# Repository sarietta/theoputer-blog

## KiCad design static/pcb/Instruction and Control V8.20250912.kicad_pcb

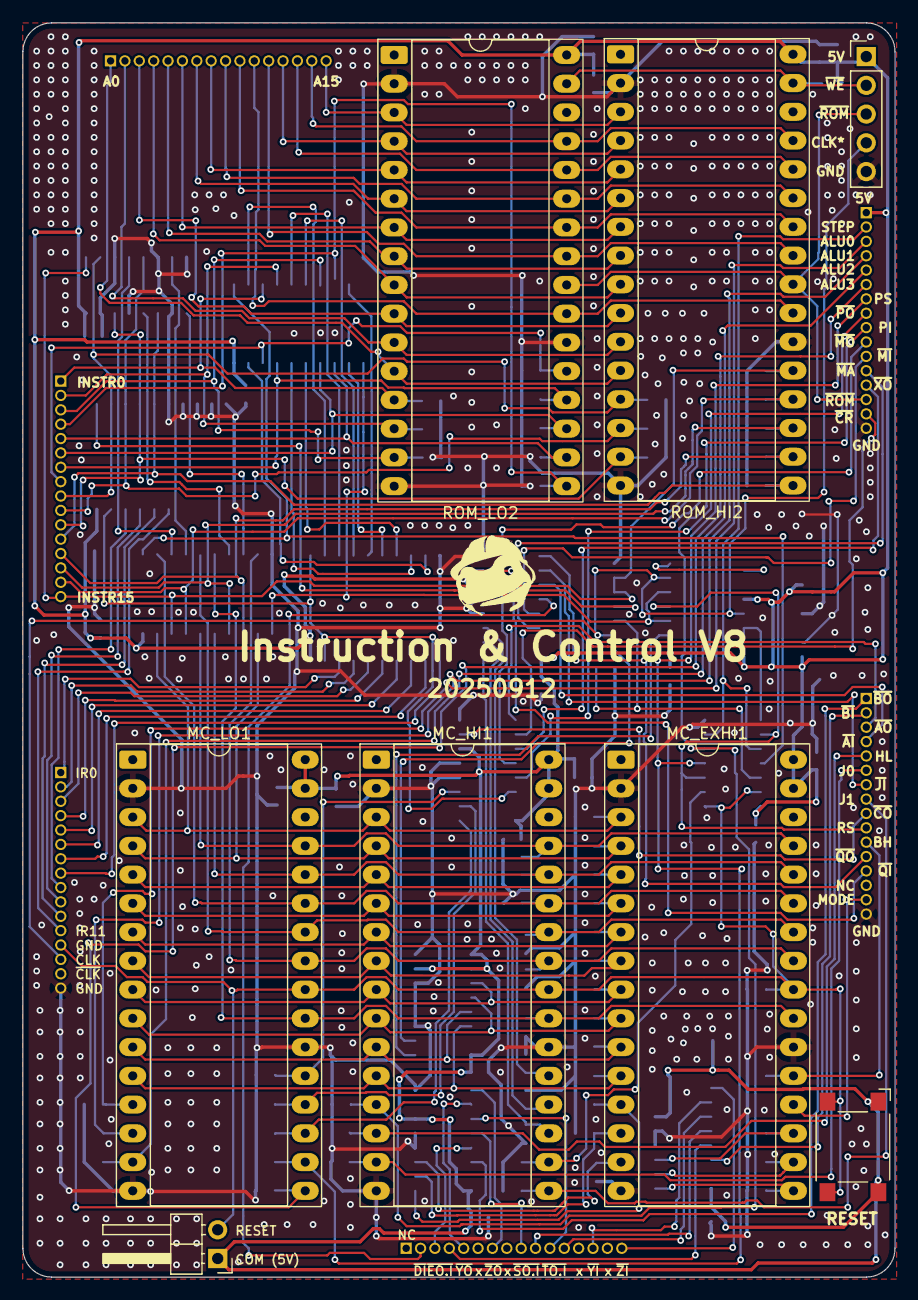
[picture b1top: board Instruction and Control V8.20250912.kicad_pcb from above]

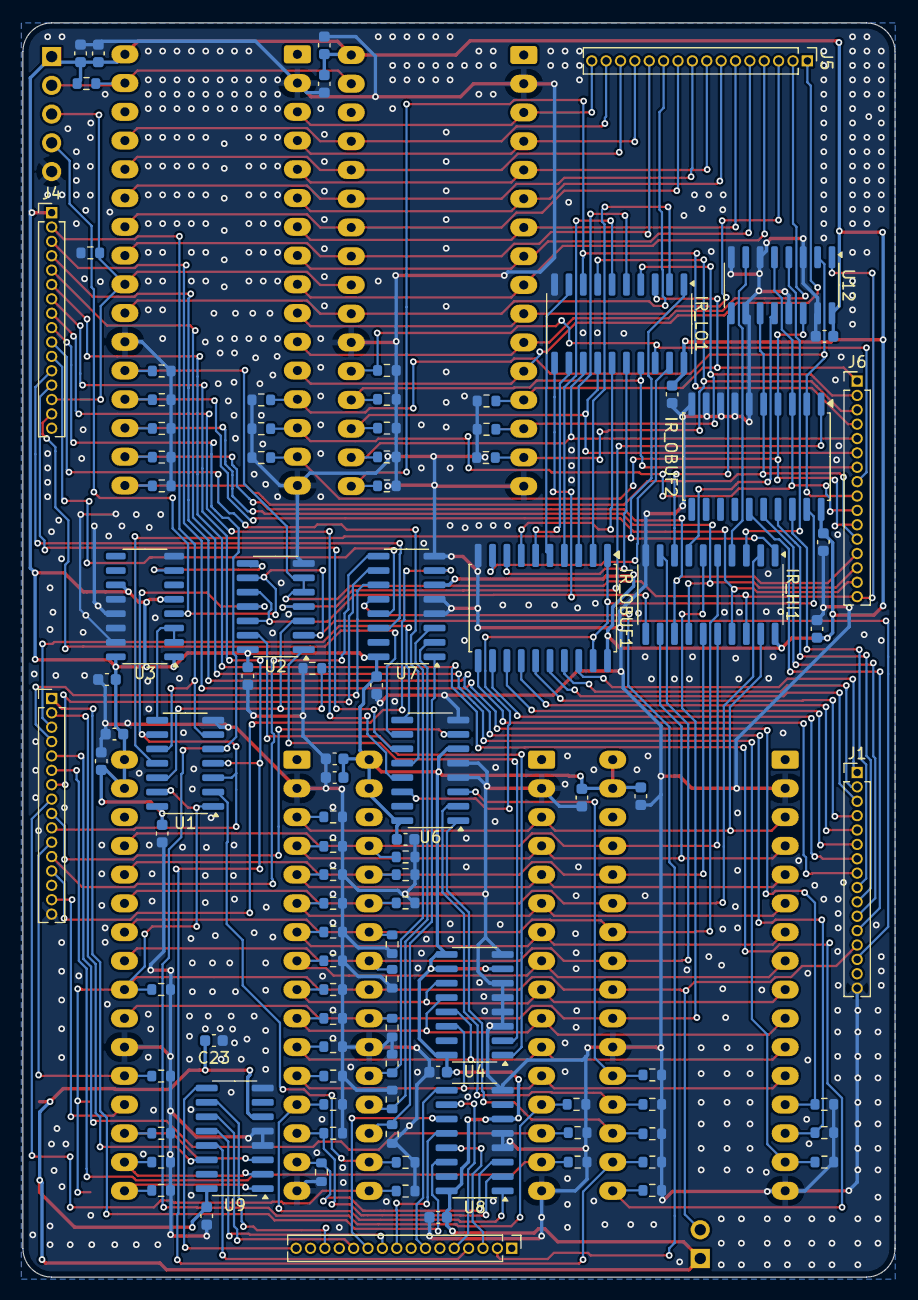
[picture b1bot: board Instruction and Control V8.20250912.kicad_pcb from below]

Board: 2 copper layers, 77.1 x 110.8 mm, 109 parts (101 on the bottom side), 138 nets.

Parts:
C1, C19, C20, C21, C22: 1uF; C_0603_1608Metric
C2, C3, C4, C5, C6, C7, C8, C9, C10, C11, C12, C13, C14, C15, C16, C17, C18, C23: 0.1uF; C_0603_1608Metric
IR_HI1: 74HCT374; SO-20_5.3x12.6mm_P1.27mm
IR_LO1: 74HCT374; SO-20_5.3x12.6mm_P1.27mm
IR_OBUF1, IR_OBUF2: 74HCT541D,653; SOIC-20W_7.5x12.8mm_P1.27mm
J1, J3, J4, J5, J6, J9: Conn_01x16; PinHeader_1x16_P1.27mm_Vertical
J2: Conn_01x05; PinHeader_1x05_P2.54mm_Vertical
J7: Conn_01x02; PinHeader_1x02_P2.54mm_Horizontal
MC_EXHI1: SST39SF010; DIP-32_W15.24mm_Socket_LongPads
MC_HI1: SST39SF010; DIP-32_W15.24mm_Socket_LongPads
MC_LO1: SST39SF010; DIP-32_W15.24mm_Socket_LongPads
R1, R3, R4, R5, R6, R7, R8, R9, R10, R11, R12, R13, R14, R15, R16, R17, R18, R19, R20, R21, R22, R23, R24, R25, R26, R27, R28, R29, R30, R31, R32, R33, R34, R35, R36, R37, R38, R39, R40, R41, R42, R47, R48, R49, R50, R51, R52, R53, R54, R55, R56, R57, R58, R59, R60, R61, R62, R66, R67: 1K; R_0603_1608Metric
ROM_HI2: SST39SF010; DIP-32_W15.24mm_Socket_LongPads
ROM_LO2: SST39SF010; DIP-32_W15.24mm_Socket_LongPads
SW1: SW_Omron_B3FS; SW_SPST_Omron_B3FS-100xP
U1: SN74ACT32DR; SOIC-14_3.9x8.7mm_P1.27mm
U2: SN74HCT02DR; SOIC-14_3.9x8.7mm_P1.27mm
U3: 74HC109D,653; SO-16_3.9x9.9mm_P1.27mm
U4: 74ACT161; SOIC-16_3.9x9.9mm_P1.27mm
U6, U7, U8, U9: SN74HCT138DR; SOIC-16_3.9x9.9mm_P1.27mm
U12: SN74HC257DR; SOIC-16_3.9x9.9mm_P1.27mm

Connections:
+5V: C1.1, C2.1, C3.1, C4.1, C5.1, C6.1, C7.1, C8.1, C9.1, C10.1, C11.1, C12.1, C13.1, C14.1, C15.1, C16.1, C17.1, C18.1, C19.1, C20.1, C21.1, C22.1, C23.1, IR_HI1.20 (VCC), IR_LO1.20 (VCC), IR_OBUF1.20 (VCC), IR_OBUF2.20 (VCC), J2.1, J4.1, J7.1, MC_EXHI1.31 (PGM), MC_EXHI1.32 (VCC), MC_HI1.31 (PGM), MC_HI1.32 (VCC), MC_LO1.31 (PGM), MC_LO1.32 (VCC), R66.2, ROM_HI2.32 (VCC), ROM_LO2.32 (VCC), SW1.1, U1.14 (VCC), U2.14 (VCC), U3.1 (~R), U3.5 (~S), U3.11 (~S), U3.16 (VCC), U4.7 (CEP), U4.9 (~PE), U4.10 (CET), U4.16 (VCC), U6.6 (E2), U6.16 (VCC), U7.6 (E2), U7.16 (VCC), U8.6 (E2), U8.16 (VCC), U9.6 (E2), U9.16 (VCC), U12.16 (VCC)
/ADDR0: J5.1, ROM_HI2.12 (A0), ROM_LO2.12 (A0)
/ADDR1: J5.2, ROM_HI2.11 (A1), ROM_LO2.11 (A1)
/ADDR2: J5.3, ROM_HI2.10 (A2), ROM_LO2.10 (A2)
/ADDR3: J5.4, ROM_HI2.9 (A3), ROM_LO2.9 (A3)
/ADDR4: J5.5, ROM_HI2.8 (A4), ROM_LO2.8 (A4)
/ADDR5: J5.6, ROM_HI2.7 (A5), ROM_LO2.7 (A5)
/ADDR6: J5.7, ROM_HI2.6 (A6), ROM_LO2.6 (A6)
/ADDR7: J5.8, ROM_HI2.5 (A7), ROM_LO2.5 (A7)
/ADDR8: J5.9, ROM_HI2.27 (A8), ROM_LO2.27 (A8)
/ADDR9: J5.10, ROM_HI2.26 (A9), ROM_LO2.26 (A9)
/ADDR10: J5.11, ROM_HI2.23 (A10), ROM_LO2.23 (A10)
/ADDR11: J5.12, ROM_HI2.25 (A11), ROM_LO2.25 (A11)
/ADDR12: J5.13, ROM_HI2.4 (A12), ROM_LO2.4 (A12)
/ADDR13: J5.14, ROM_HI2.28 (A13), ROM_LO2.28 (A13)
/ADDR14: J5.15, ROM_HI2.29 (A14), ROM_LO2.29 (A14)
/ADDR15: J5.16, ROM_HI2.3 (A15), ROM_LO2.3 (A15)
/ALU0: J4.3, MC_LO1.13 (D0), R38.1
/ALU1: J4.4, MC_LO1.14 (D1), R36.1
/ALU2: J4.5, MC_LO1.15 (D2), R34.1
/ALU3: J4.6, MC_LO1.17 (D3), R33.1
/BO_HI: J3.11, MC_EXHI1.21 (D7), R32.1
/CLK: J1.14, J2.4, U2.2, U2.9, U3.4 (C)
/DISABLE_ROM: J2.3, J4.14, R67.2, ROM_HI2.24 (OE), ROM_LO2.24 (OE)
/EXEC_MODE: J3.15, MC_EXHI1.20 (D6)
/EXT_IN0: MC_EXHI1.17 (D3), R39.1, U9.1 (A0)
/EXT_IN1: MC_EXHI1.18 (D4), R37.1, U9.2 (A1)
/EXT_IN2: MC_EXHI1.19 (D5), R35.1, U9.3 (A2)
/EXT_OUT0: MC_EXHI1.13 (D0), R42.1, U8.1 (A0)
/EXT_OUT1: MC_EXHI1.14 (D1), R41.1, U8.2 (A1)
/EXT_OUT2: MC_EXHI1.15 (D2), R40.1, U8.3 (A2)
/HL: J3.5, MC_HI1.14 (D1), R26.1
/IN0: MC_HI1.19 (D5), R22.1, U7.1 (A0)
/IN1: MC_HI1.20 (D6), R21.1, U7.2 (A1)
/IN2: MC_HI1.21 (D7), R20.1, U7.3 (A2)
/INHIBIT_MC: R1.1, U1.12, U2.3
/INSTR0: IR_LO1.3 (D0), J6.1, R62.1, ROM_LO2.13 (D0)
/INSTR1: IR_LO1.4 (D1), J6.2, R61.1, ROM_LO2.14 (D1)
/INSTR2: IR_LO1.7 (D2), J6.3, R60.1, ROM_LO2.15 (D2)
/INSTR3: IR_LO1.8 (D3), J6.4, R59.1, ROM_LO2.17 (D3)
/INSTR4: IR_LO1.13 (D4), J6.5, R58.1, ROM_LO2.18 (D4)
/INSTR5: IR_LO1.14 (D5), J6.6, R57.1, ROM_LO2.19 (D5)
/INSTR6: IR_LO1.17 (D6), J6.7, R56.1, ROM_LO2.20 (D6)
/INSTR7: IR_LO1.18 (D7), J6.8, R55.1, ROM_LO2.21 (D7)
/INSTR8: IR_OBUF2.2 (A0), J6.9, R54.1, ROM_HI2.13 (D0), U12.2 (I0a)
/INSTR9: IR_OBUF2.3 (A1), J6.10, R53.1, ROM_HI2.14 (D1), U12.5 (I0b)
/INSTR10: IR_OBUF2.4 (A2), J6.11, R52.1, ROM_HI2.15 (D2), U12.14 (I0c)
/INSTR11: IR_OBUF2.5 (A3), J6.12, R51.1, ROM_HI2.17 (D3), U12.11 (I0d)
/INSTR12: IR_HI1.13 (D4), J6.13, R50.1, ROM_HI2.18 (D4)
/INSTR13: IR_HI1.14 (D5), J6.14, R49.1, ROM_HI2.19 (D5)
/INSTR14: IR_HI1.17 (D6), J6.15, R48.1, ROM_HI2.20 (D6)
/INSTR15: IR_HI1.18 (D7), J6.16, R47.1, ROM_HI2.21 (D7), U2.5, U2.6, U12.1 (S)
/IR_OUT0: IR_OBUF1.18 (Y0), J1.1
/IR_OUT1: IR_OBUF1.17 (Y1), J1.2
/IR_OUT2: IR_OBUF1.16 (Y2), J1.3
/IR_OUT3: IR_OBUF1.15 (Y3), J1.4
/IR_OUT4: IR_OBUF1.14 (Y4), J1.5
/IR_OUT5: IR_OBUF1.13 (Y5), J1.6
/IR_OUT6: IR_OBUF1.12 (Y6), J1.7
/IR_OUT7: IR_OBUF1.11 (Y7), J1.8
/IR_OUT8: IR_OBUF2.18 (Y0), J1.9
/IR_OUT9: IR_OBUF2.17 (Y1), J1.10
/IR_OUT10: IR_OBUF2.16 (Y2), J1.11
/IR_OUT11: IR_OBUF2.15 (Y3), J1.12
/J0: J3.6, MC_HI1.15 (D2), R25.1
/J1: J3.8, MC_HI1.17 (D3), R24.1
/MC0: MC_EXHI1.12 (A0), MC_HI1.12 (A0), MC_LO1.12 (A0), R19.1, U4.14 (Q0)
/MC1: MC_EXHI1.11 (A1), MC_HI1.11 (A1), MC_LO1.11 (A1), R18.1, U4.13 (Q1)
/MC2: MC_EXHI1.10 (A2), MC_HI1.10 (A2), MC_LO1.10 (A2), R17.1, U4.12 (Q2)
/MC3: MC_EXHI1.9 (A3), MC_HI1.9 (A3), MC_LO1.9 (A3), R16.1, U4.11 (Q3)
/MC4: MC_EXHI1.8 (A4), MC_HI1.8 (A4), MC_LO1.8 (A4), R15.1
/MC5: MC_EXHI1.7 (A5), MC_HI1.7 (A5), MC_LO1.7 (A5), R14.1
/MC6: MC_EXHI1.6 (A6), MC_HI1.6 (A6), MC_LO1.6 (A6), R13.1
/MC7: MC_EXHI1.5 (A7), MC_HI1.5 (A7), MC_LO1.5 (A7), R12.1
/MC8: IR_HI1.2 (O0), MC_EXHI1.27 (A8), MC_HI1.27 (A8), MC_LO1.27 (A8), R11.1
/MC9: IR_HI1.5 (O1), MC_EXHI1.26 (A9), MC_HI1.26 (A9), MC_LO1.26 (A9), R10.1
/MC10: IR_HI1.6 (O2), MC_EXHI1.23 (A10), MC_HI1.23 (A10), MC_LO1.23 (A10), R9.1
/MC11: IR_HI1.9 (O3), MC_EXHI1.25 (A11), MC_HI1.25 (A11), MC_LO1.25 (A11), R8.1
/MC12: IR_HI1.12 (O4), MC_EXHI1.4 (A12), MC_HI1.4 (A12), MC_LO1.4 (A12), R7.1
/MC13: IR_HI1.15 (O5), MC_EXHI1.28 (A13), MC_HI1.28 (A13), MC_LO1.28 (A13), R6.1
/MC14: IR_HI1.16 (O6), MC_EXHI1.29 (A14), MC_HI1.29 (A14), MC_LO1.29 (A14), R5.1
/MC15: IR_HI1.19 (O7), MC_EXHI1.3 (A15), MC_HI1.3 (A15), MC_LO1.3 (A15), R4.1
/OUT0: MC_LO1.19 (D5), R30.1, U6.1 (A0)
/OUT1: MC_LO1.20 (D6), R29.1, U6.2 (A1)
/OUT2: MC_LO1.21 (D7), R28.1, U6.3 (A2)
/PI: J4.9, MC_HI1.13 (D0), R27.1, U1.5
/PS: J4.7, MC_LO1.18 (D4), R31.1, U1.4
/RS: J3.10, U1.3, U1.9, U2.11
/RS1^{*}: MC_HI1.18 (D4), R23.1, U1.2
/RS2^{*}: J1.13, J7.2, MC_EXHI1.24 (OE), MC_HI1.24 (OE), MC_LO1.24 (OE), R3.2, SW1.2, U1.1, U1.13
/STEP: J4.2, U1.6, U1.10
/~AI: J3.4, U7.11 (~Y4)
/~AO: J3.3, U6.9 (~Y6)
/~BI: J3.2, U9.14 (~Y1)
/~BO: J3.1, U8.14 (~Y1)
/~CO: J3.9, U6.7 (~Y7)
/~CR: J4.15, U6.10 (~Y5)
/~DI: J9.2, U7.12 (~Y3)
/~EI: J9.4, U9.13 (~Y2)
/~EO: J9.3, U8.13 (~Y2)
/~IO: IR_OBUF1.1 (G1), IR_OBUF1.19 (G2), IR_OBUF2.19 (G2), U6.14 (~Y1)
/~JI: J3.7, U7.10 (~Y5)
/~MA: J4.12, U7.14 (~Y1)
/~MI: J4.11, U7.13 (~Y2)
/~MO: J4.10, U6.12 (~Y3)
/~PO: J4.8, U6.13 (~Y2)
/~QI: J3.13, U7.7 (~Y7)
/~QO: J3.12, U7.9 (~Y6)
/~RESET_MC_COUNTER_NEXT_DOWNCLK: U2.8, U3.7 (~Q)
/~RESET_MC_COUNTER: U2.13, U4.1 (~MR)
/~ROM_WE: J2.2, R66.1, ROM_HI2.31 (PGM), ROM_LO2.31 (PGM)
/~SI: J9.10, U9.12 (~Y3)
/~SO: J9.9, U8.12 (~Y3)
/~TI: J9.12, U9.11 (~Y4)
/~TO: J9.11, U8.11 (~Y4)
/~XO: J4.13, U6.11 (~Y4)
/~YI: J9.14, U9.10 (~Y5)
/~YO: J9.5, U8.10 (~Y5)
/~ZI: J9.16, U9.9 (~Y6)
/~ZO: J9.7, U8.9 (~Y6)
/↓LATCH_INSTRUCTION: IR_HI1.11 (Cp), IR_LO1.11 (Cp), U2.10, U2.12
GND: C1.2, C2.2, C3.2, C4.2, C5.2, C6.2, C7.2, C8.2, C9.2, C10.2, C11.2, C12.2, C13.2, C14.2, C15.2, C16.2, C17.2, C18.2, C19.2, C20.2, C21.2, C22.2, C23.2, IR_HI1.10 (GND), IR_LO1.10 (GND), IR_OBUF1.10 (GND), IR_OBUF2.6 (A4), IR_OBUF2.7 (A5), IR_OBUF2.8 (A6), IR_OBUF2.9 (A7), IR_OBUF2.10 (GND), J1.16, J2.5, J3.16, J4.16, MC_EXHI1.2 (A16), MC_EXHI1.16 (GND), MC_EXHI1.22 (CE), MC_HI1.2 (A16), MC_HI1.16 (GND), MC_HI1.22 (CE), MC_LO1.2 (A16), MC_LO1.16 (GND), MC_LO1.22 (CE), R1.2, R3.1, R4.2, R5.2, R6.2, R7.2, R8.2, R9.2, R10.2, R11.2, R12.2, R13.2, R14.2, R15.2, R16.2, R17.2, R18.2, R19.2, R20.2, R21.2, R22.2, R23.2, R24.2, R25.2, R26.2, R27.2, R28.2, R29.2, R30.2, R31.2, R32.2, R33.2, R34.2, R35.2, R36.2, R37.2, R38.2, R39.2, R40.2, R41.2, R42.2, R47.2, R48.2, R49.2, R50.2, R51.2, R52.2, R53.2, R54.2, R55.2, R56.2, R57.2, R58.2, R59.2, R60.2, R61.2, R62.2, R67.1, ROM_HI2.2 (A16), ROM_HI2.16 (GND), ROM_HI2.22 (CE), ROM_LO2.2 (A16), ROM_LO2.16 (GND), ROM_LO2.22 (CE), U1.7 (GND), U2.7 (GND), U3.8 (GND), U3.12 (C), U3.13 (~K), U3.14 (J), U3.15 (~R), U4.3 (D0), U4.4 (D1), U4.5 (D2), U4.6 (D3), U4.8 (GND), U6.4 (~E0), U6.5 (~E1), U6.8 (GND), U7.4 (~E0), U7.5 (~E1), U7.8 (GND), U8.4 (~E0), U8.5 (~E1), U8.8 (GND), U9.4 (~E0), U9.5 (~E1), U9.8 (GND), U12.3 (I1a), U12.6 (I1b), U12.8 (GND), U12.10 (I1d), U12.13 (I1c), U12.15 (OE)
unnamed: IR_HI1.3 (D0), U12.4 (Za)
unnamed: IR_HI1.4 (D1), U12.7 (Zb)
unnamed: IR_HI1.7 (D2), U12.12 (Zc)
unnamed: IR_HI1.8 (D3), U12.9 (Zd)
unnamed: IR_HI1.1 (OE), IR_LO1.1 (OE), U1.11
unnamed: IR_LO1.2 (O0), IR_OBUF1.2 (A0)
unnamed: IR_LO1.5 (O1), IR_OBUF1.3 (A1)
unnamed: IR_LO1.6 (O2), IR_OBUF1.4 (A2)
unnamed: IR_LO1.9 (O3), IR_OBUF1.5 (A3)
unnamed: IR_LO1.12 (O4), IR_OBUF1.6 (A4)
unnamed: IR_LO1.15 (O5), IR_OBUF1.7 (A5)
unnamed: IR_LO1.16 (O6), IR_OBUF1.8 (A6)
unnamed: IR_LO1.19 (O7), IR_OBUF1.9 (A7)
unnamed: IR_OBUF2.1 (G1), U2.4
unnamed: U1.8, U3.2 (J), U3.3 (~K)
unnamed: U2.1, U4.2 (CP)

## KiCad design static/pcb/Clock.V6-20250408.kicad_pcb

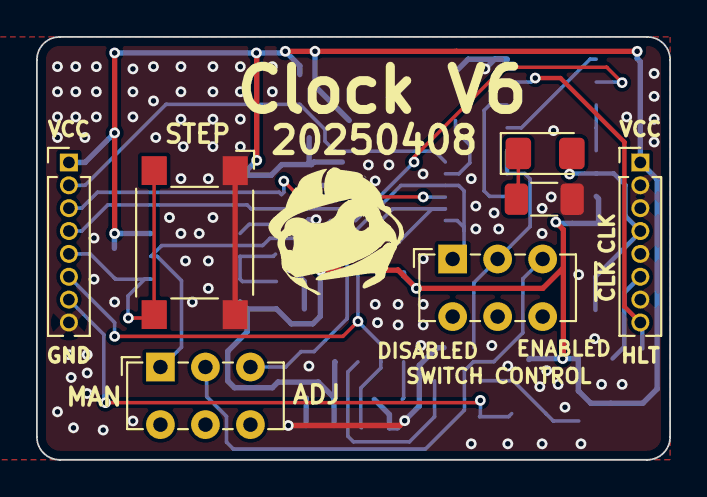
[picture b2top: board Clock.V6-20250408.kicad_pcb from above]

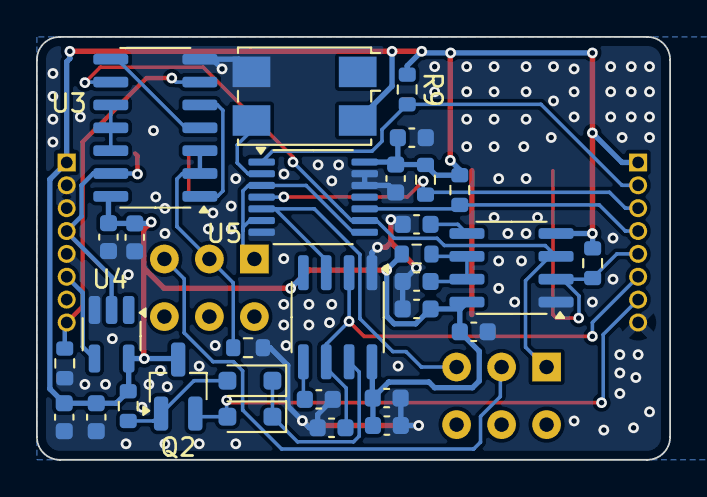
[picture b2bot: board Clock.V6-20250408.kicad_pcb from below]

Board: 4 copper layers, 35.2 x 23.5 mm, 38 parts (31 on the bottom side), 26 nets.

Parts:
C1, C2, C5, C10, C12, C14: 1uF; C_0603_1608Metric
C3, C6: 0.01uF; C_0603_1608Metric
C4, C9, C11, C13, C15: 0.1uF; C_0603_1608Metric
C7: 22uF; C_0603_1608Metric
D1, D2: 1N5819WS; D_SOD-323_HandSoldering
D3: LED; LED_1206_3216Metric_Pad1.42x1.75mm_HandSolder
J7, J8: Conn_01x08; PinHeader_1x08_P1.27mm_Vertical
Q2: MMBT3904; SOT-23_Handsoldering
R1, R5, R6, R7, R8, R9: 1K; R_0603_1608Metric
R2, R3: 10K; R_0603_1608Metric
R4: 1K; R_1206_3216Metric_Pad1.30x1.75mm_HandSolder
SW_EN1: SW_SPDT; SW_E-Switch_EG1271_SPDT
SW_MAN_OR_ADJ1: SW_SPDT; SW_E-Switch_EG1271_SPDT
SW_STEP_1: SW_Omron_B3FS; SW_SPST_Omron_B3FS-100xP
U1, U2: TLC555xD; SOIC-8_3.9x4.9mm_P1.27mm
U3: SN74HCT02DR; SOIC-14_3.9x8.7mm_P1.27mm
U4: SN74AHCT1G04DBVR; SOT-23-5_HandSoldering
U5: SN74AHCT125PWR; TSSOP-14_4.4x5mm_P0.65mm
X1: S7D1.843200A20F30T; Crystal_SMD_7050-4Pin_7.0x5.0mm

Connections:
+5V: C1.1, C4.1, C5.1, C9.1, C10.1, C11.1, C12.1, C13.1, C14.1, C15.1, J7.1, J8.1, Q2.3 (C), R1.1, R2.1, R3.1, R6.1, R8.1, R9.1, U1.4 (R), U1.8 (VCC), U2.4 (R), U2.8 (VCC), U3.14 (VCC), U4.5 (VCC), U5.14 (VCC), X1.4 (VCC)
/ADJ_GND: C2.1, J7.6, U1.2 (TR), U1.6 (THR)
/ADJ_VCC: D2.2 (A), J7.7, Q2.2 (E)
/CLK: D3.2 (A), J8.4, U3.13, U4.2
/HLT: J8.8, R5.1, U3.6
/MODE_ADJUSTABLE: SW_MAN_OR_ADJ1.3 (C), U1.3 (Q), U5.5
/MODE_COM: R7.1, SW_EN1.2 (B), U3.2, U3.3
/MODE_MANUAL: SW_MAN_OR_ADJ1.1 (A), U2.3 (Q), U3.9, U5.9
/MODE_OSCILLATOR: U5.2, X1.3 (OUT)
/~CLK: J8.6, U4.4
/~MODE_ADJUSTABLE_EN: J7.3, R8.2, U5.4
/~MODE_MANUAL_EN: J7.4, R6.2, U5.10
/~MODE_OSCILLATOR_EN: J7.2, R9.2, U5.1
/~STEP_EN: J7.5, R3.2, SW_STEP_1.2, U2.2 (TR)
GND: C1.2, C2.2, C3.2, C4.2, C5.2, C6.2, C7.2, C9.2, C10.2, C11.2, C12.2, C13.2, C14.2, C15.2, J7.8, J8.2, J8.3, J8.5, J8.7, R4.2, R5.2, R7.2, SW_STEP_1.1, U1.1 (GND), U2.1 (GND), U3.7 (GND), U4.3 (GND), U5.7 (GND), U5.12, U5.13, X1.2 (GND)
unnamed: D1.2 (A), Q2.1 (B), R1.2
unnamed: D1.1 (K), D2.1 (K), U1.7 (DIS)
unnamed: D3.1 (K), R4.1
unnamed: SW_EN1.1 (A), U5.3, U5.6, U5.8
unnamed: SW_EN1.3 (C), SW_MAN_OR_ADJ1.2 (B)
unnamed: C3.1, U1.5 (CV)
unnamed: C6.1, U2.5 (CV)
unnamed: C7.1, R2.2, U2.6 (THR), U2.7 (DIS)
unnamed: U3.1, U3.5
unnamed: U3.4, U3.8
unnamed: U3.10, U3.11, U3.12

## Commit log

2024-10-09 First blog post, weeee. About the IRQ
2024-10-10 Adjustments originally made to the theme directly now moved out into the main repo for isolation
2024-10-10 Correct baseurl
2024-10-10 Some touchups and general polish
2024-10-10 Fixed broken ref
2024-10-10 New images for the IRQ post
2024-11-01 Updates for new content
2024-11-29 New blog post and a tool for generating approximations of square waves
2024-12-30 Finished the transmission line blog post, and some other semi-minor updates
2024-12-30 Adding in commenting via giscus
2024-12-30 Working on a new post and publishing transmission reflections post
2024-12-30 Better handling of missing post links
2024-12-30 Little fixup
2024-12-30 Removed incorrectly setup post
2024-12-30 Typo
2024-12-30 Missing images
2025-01-04 Updated posts
2025-09-13 Working on ALU page
2025-09-15 New posts about the ALU
2025-09-15 Some grammar issues on the ALU subtraction post
2025-09-16 New post about the clock, WIP
2025-09-22 New posts. Clocks. And web components
2025-09-24 Clock extras draft is done
2025-09-26 Working on clock 4 layer post
2025-09-26 Moved component imports to local repo
2025-09-28 New post about ground bounce
2025-09-29 Finishing up ground noise
2025-09-29 Update theme submodule
2025-09-29 Updated theme submodule
2025-09-29 Git submodule
2025-09-29 Moving away from annoyinf git submodule for theme
2025-09-29 Re-adding theme directly versus submodules
2025-09-29 Publishing alu subtraction post
2025-10-08 Static files
2025-10-08 Better UX for svg viewer
2025-10-08 Mooar post content. Daughter board and simulator info
2025-10-09 Updated some theme files
2025-10-09 Working on content
2025-10-11 Improvements to the kicad viewer and the svg viewer
2025-10-11 Working on the daughter board post still
2025-10-12 Finished daughter board post
2025-10-12 Added a few nice ergonomics: categories, search, header images
2025-10-12 Some light content updates and added a nice infinite scroll lib
2025-10-13 Ignore mac metadata files
2025-10-13 Better circuitjs support from a local app. Also some new content on registers
2025-10-14 New overview post
2025-10-15 Some updates to the databus post
2025-10-15 Missing images'
2025-10-17 Improvements to the circuit web component to lazily load the project files
2025-10-17 Finishing out the databus post
2025-10-18 RAM post finalization
2025-10-18 Grammar on the ram post
2025-10-18 Adding in tags
2025-10-18 Fixed pagination showing on infinite scroll and added animated gif for simulator post
2025-10-18 Register description
2025-10-25 New posts about the first operation and program counter
2025-10-26 Working on the I&C board post, but also adding in some empty content to help keep track of what I need to write
2025-11-04 New post sfor the instruction and control board, plus a lot of grammar and spelling fixes
2025-11-04 New tool for making gifs
2025-11-04 Publishing the I&C post
2025-11-04 Header image for the I&C post and made article list clickable
2025-11-05 Starting C compiler post
2025-11-11 Working on compiler posts
2025-11-11 Description for the assembler post
2025-11-21 Draft of the compiler intro
2025-11-22 Updates to C compiler intro
2025-11-22 C compiler intro description and header image
2025-12-05 Finished recursion post and working on cish grammar post
2025-12-06 Nice notice boxes
